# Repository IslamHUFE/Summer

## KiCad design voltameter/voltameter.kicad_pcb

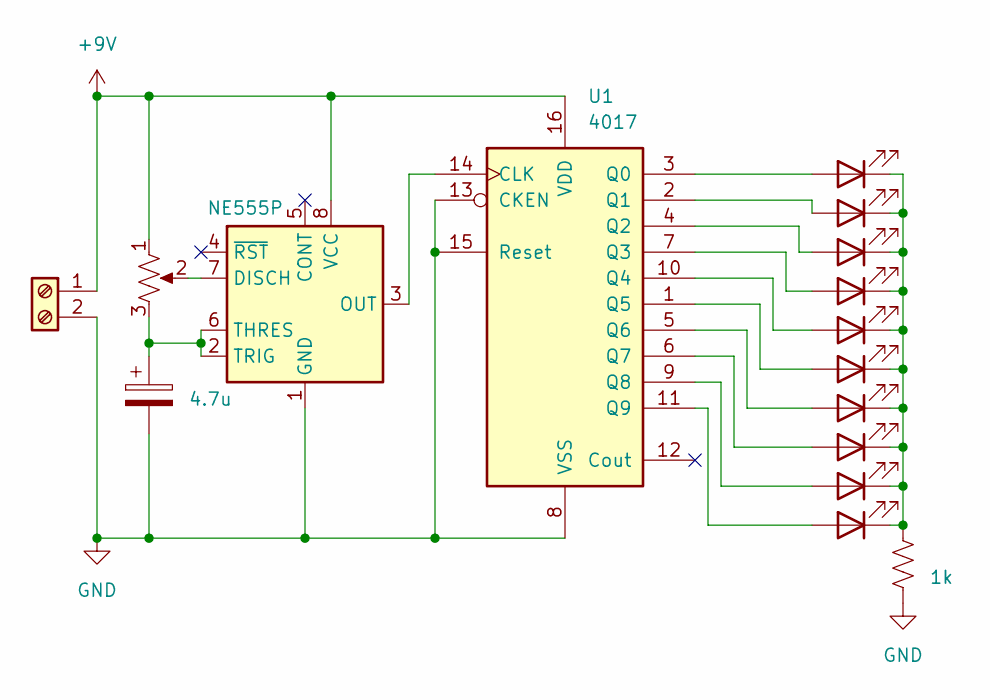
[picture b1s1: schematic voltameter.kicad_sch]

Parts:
C1: 4.7u; CP_Radial_D5.0mm_P2.50mm
D1, D2, D3, D4, D5, D6, D7, D8, D9, D10: LED; LED_D5.0mm
J1: Screw_Terminal_01x02; JST_EH_S2B-EH_1x02_P2.50mm_Horizontal
R1: 1k; R_Axial_DIN0204_L3.6mm_D1.6mm_P5.08mm_Horizontal
RV2: R_Potentiometer_US; Potentiometer_Piher_PT-6-V_Vertical
U1: 4017; DIP-16_W7.62mm
U2: NE555P; DIP-8_W7.62mm

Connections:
+9V: J1.1, RV2.1, U1.16 (VDD), U2.8 (VCC)
GND: C1.2, J1.2, R1.2, U1.8 (VSS), U1.13 (CKEN), U1.15 (Reset), U2.1 (GND)
unnamed: D1.2 (A), U1.3 (Q0)
unnamed: D1.1 (K), D2.1 (K), D3.1 (K), D4.1 (K), D5.1 (K), D6.1 (K), D7.1 (K), D8.1 (K), D9.1 (K), D10.1 (K), R1.1
unnamed: D2.2 (A), U1.2 (Q1)
unnamed: D3.2 (A), U1.4 (Q2)
unnamed: D4.2 (A), U1.7 (Q3)
unnamed: D5.2 (A), U1.10 (Q4)
unnamed: D6.2 (A), U1.1 (Q5)
unnamed: D7.2 (A), U1.5 (Q6)
unnamed: D8.2 (A), U1.6 (Q7)
unnamed: D9.2 (A), U1.9 (Q8)
unnamed: D10.2 (A), U1.11 (Q9)
unnamed: U1.14 (CLK), U2.3 (OUT)
unnamed: RV2.2, U2.7 (DISCH)
unnamed: C1.1, RV2.3, U2.2 (TRIG), U2.6 (THRES)

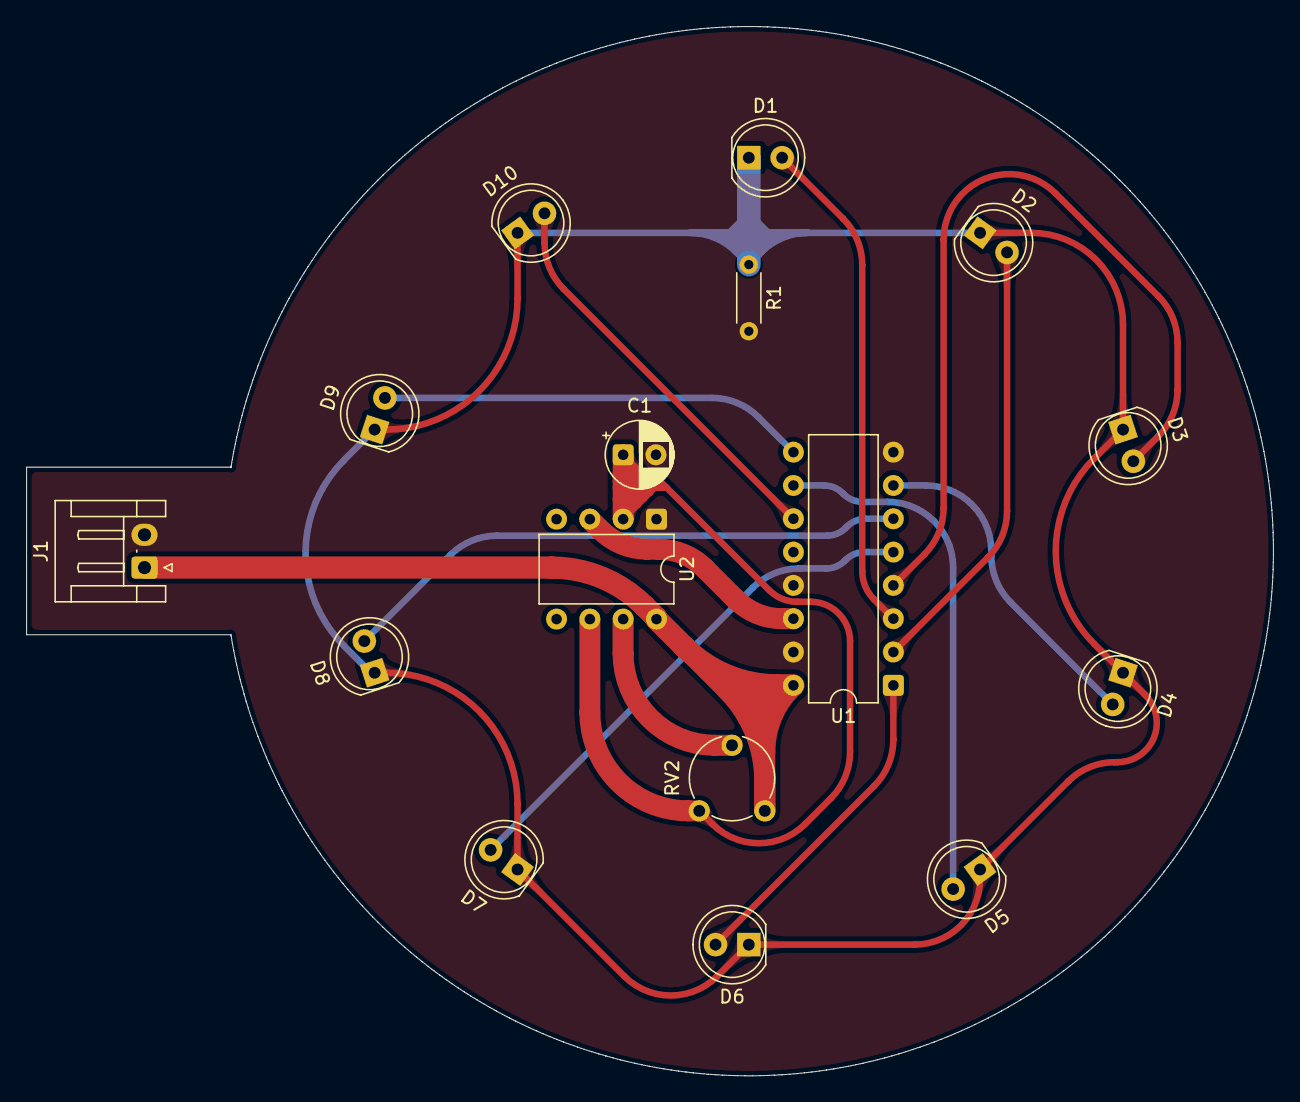
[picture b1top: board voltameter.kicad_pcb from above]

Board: 4 copper layers, 95.1 x 80.0 mm, 16 parts (0 on the bottom side), 16 nets.

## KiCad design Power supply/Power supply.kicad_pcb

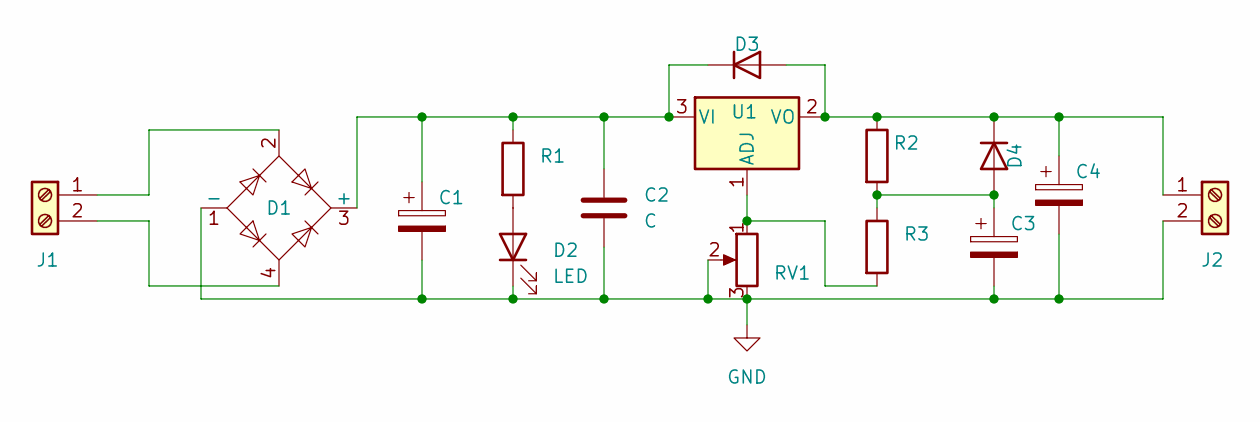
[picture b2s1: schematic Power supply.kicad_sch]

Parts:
C1: C_Polarized; CP_Radial_D12.5mm_P7.50mm
C2: C; C_Disc_D3.0mm_W1.6mm_P2.50mm
C3, C4: C_Polarized; CP_Radial_D8.0mm_P3.50mm
D1: B40C2300-1500B; Diode_Bridge_19.0x3.5x10.0mm_P5.0mm
D2: LED; LED_D3.0mm
D3, D4: 1N4007; D_DO-41_SOD81_P10.16mm_Horizontal
J1, J2: Screw_Terminal_01x02; TerminalBlock_MaiXu_MX126-5.0-02P_1x02_P5.00mm
R1, R2, R3: R; R_Axial_DIN0204_L3.6mm_D1.6mm_P5.08mm_Horizontal
RV1: R_Potentiometer; Potentiometer_Alps_RK163_Single_Horizontal
U1: LM317_TO-220; TO-220-3_Vertical

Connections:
GND: C1.2, C2.2, C3.2, C4.2, D1.1 (-), D2.1 (K), J2.2, RV1.2, RV1.3
unnamed: C1.1, C2.1, D1.3 (+), D3.1 (K), R1.1, U1.3 (VI)
unnamed: D2.2 (A), R1.2
unnamed: C4.1, D3.2 (A), D4.1 (K), J2.1, R2.1, U1.2 (VO)
unnamed: C3.1, D4.2 (A), R2.2, R3.1
unnamed: D1.2, J1.1
unnamed: D1.4, J1.2
unnamed: R3.2, RV1.1, U1.1 (ADJ)

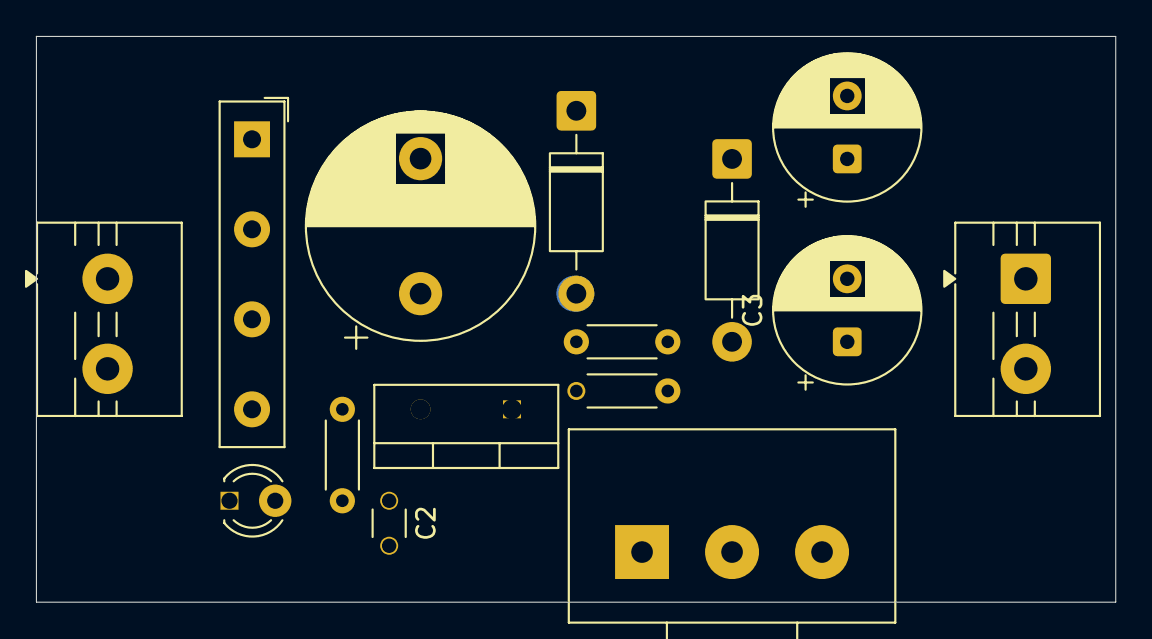
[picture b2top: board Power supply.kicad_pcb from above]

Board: 2 copper layers, 60.0 x 31.4 mm, 15 parts (0 on the bottom side), 8 nets.

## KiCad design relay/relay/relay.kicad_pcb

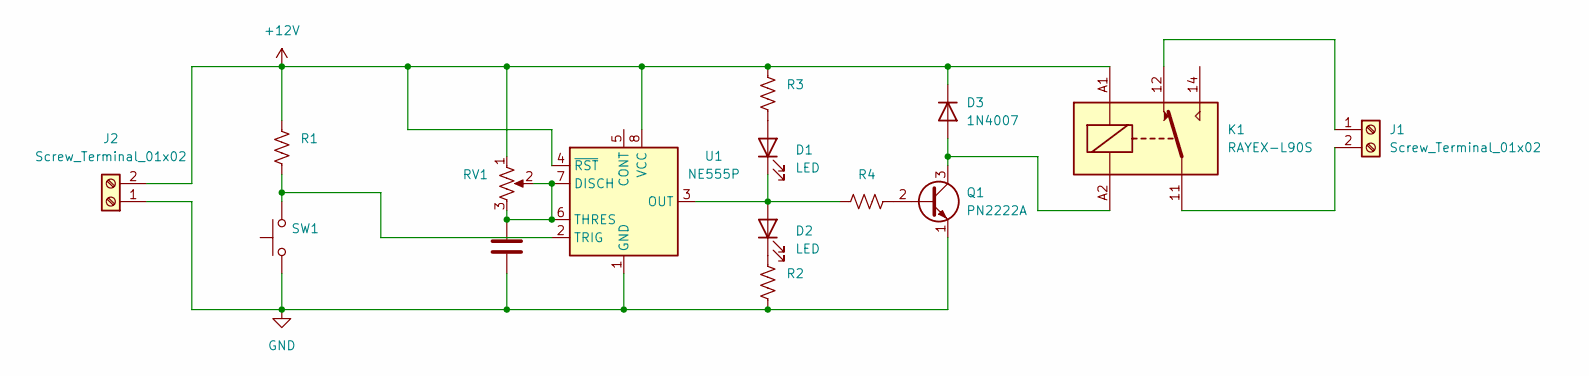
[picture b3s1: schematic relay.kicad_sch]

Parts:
C1: C; CP_Radial_D8.0mm_P5.00mm
D1, D2: LED; LED_D5.0mm
D3: 1N4007; D_DO-41_SOD81_P10.16mm_Horizontal
J1: Screw_Terminal_01x02; TerminalBlock_MaiXu_MX126-5.0-02P_1x02_P5.00mm
J2: Screw_Terminal_01x02; AMASS_XT60-F_1x02_P7.20mm_Vertical
K1: RAYEX-L90S; Relay_SPDT_RAYEX-L90S
Q1: PN2222A; TO-92_Inline
R1, R2, R3, R4: R_US; R_Axial_DIN0204_L3.6mm_D1.6mm_P5.08mm_Horizontal
RV1: R_Potentiometer_US; Potentiometer_Alps_RK163_Single_Horizontal
SW1: SW_Push; SW_PUSH_6mm_H7.3mm
U1: NE555P; DIP-8_W7.62mm

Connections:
+12V: D3.1 (K), J2.2, K1.A1, R1.1, R3.1, RV1.1, U1.4 (~RST), U1.8 (VCC)
GND: C1.2, J2.1, Q1.1 (E), R2.2, SW1.1, U1.1 (GND)
unnamed: D1.2 (A), R3.2
unnamed: D1.1 (K), D2.2 (A), R4.1, U1.3 (OUT)
unnamed: D2.1 (K), R2.1
unnamed: D3.2 (A), K1.A2, Q1.3 (C)
unnamed: J1.1, K1.12
unnamed: J1.2, K1.11
unnamed: Q1.2 (B), R4.2
unnamed: C1.1, RV1.2, RV1.3, U1.6 (THRES), U1.7 (DISCH)
unnamed: R1.2, SW1.2, U1.2 (TRIG)

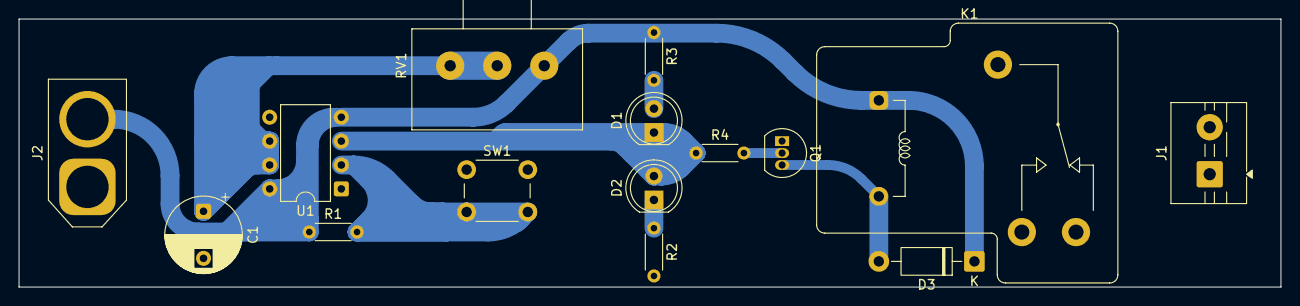
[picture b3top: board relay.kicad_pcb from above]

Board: 2 copper layers, 134.1 x 28.5 mm, 15 parts (0 on the bottom side), 11 nets.
